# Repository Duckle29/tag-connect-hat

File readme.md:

# Tag connect hat
A hat for a Rasperry Pi, for programming ISP targets with the TC2030-MCP cable

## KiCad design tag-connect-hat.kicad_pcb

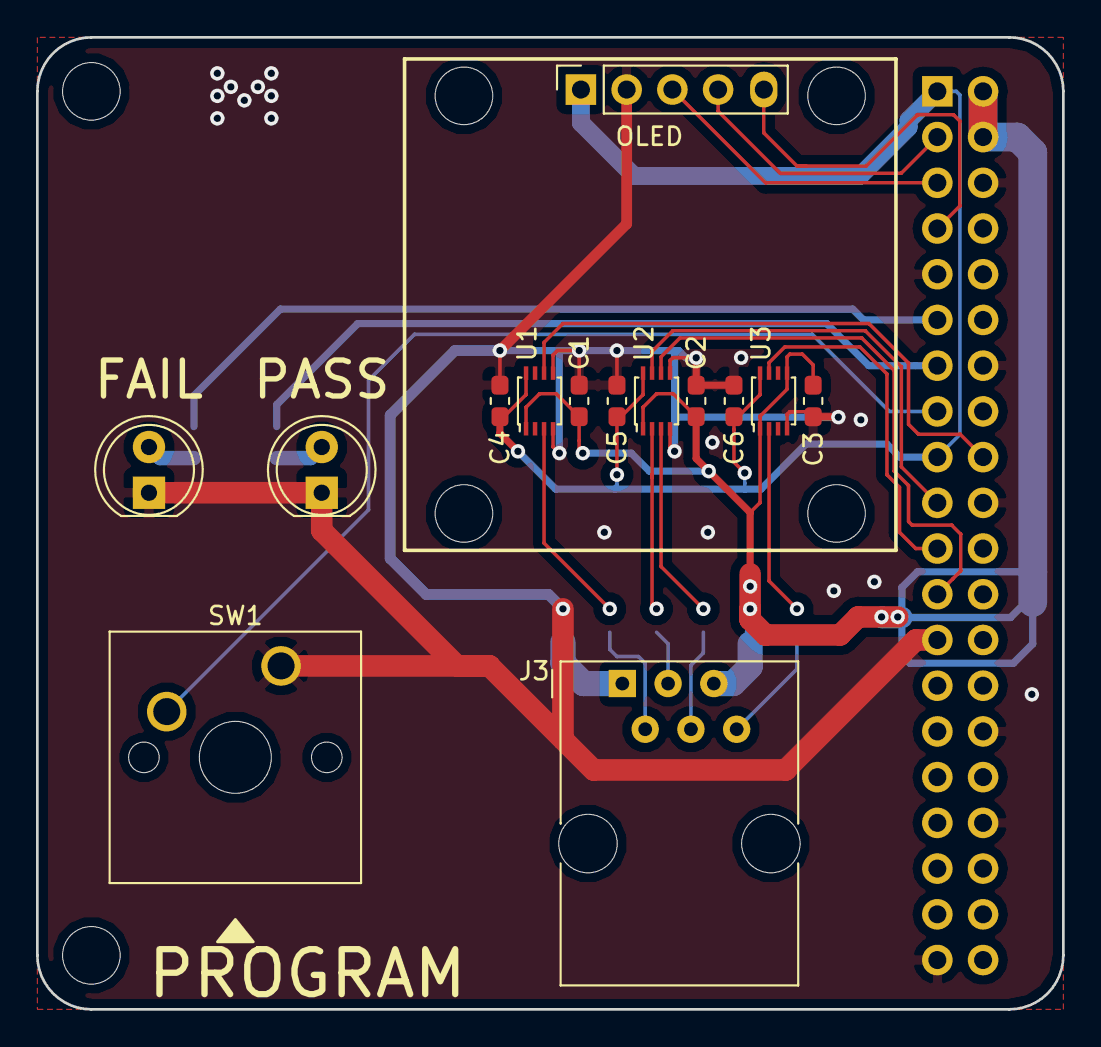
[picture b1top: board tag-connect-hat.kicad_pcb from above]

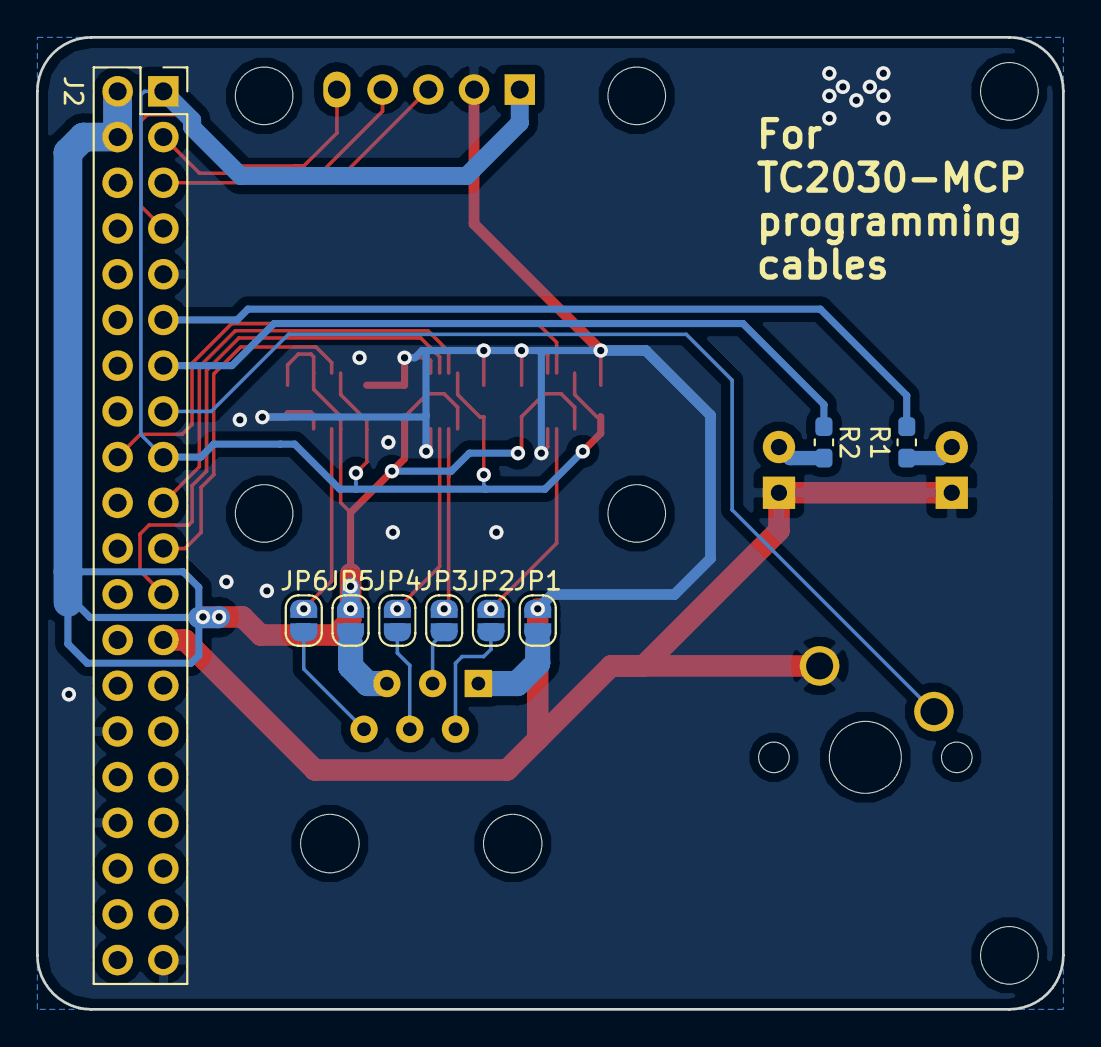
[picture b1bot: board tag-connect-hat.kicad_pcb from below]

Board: 2 copper layers, 57.0 x 54.0 mm, 23 parts (9 on the bottom side), 25 nets.

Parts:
C1, C2, C3, C4, C5, C6: 100nF; C_0603_1608Metric_Pad1.05x0.95mm_HandSolder
D1: Red; LED_D5.0mm_Clear
D2: Green; LED_D5.0mm_Clear
J1: OLED; PinSocket_1x05_P2.54mm_Vertical
J2: Raspberry_Pi_2_3; PinSocket_2x20_P2.54mm_Vertical
J3: RJ12_Shielded; RJ12_Amphenol_54601
JP1, JP2, JP3, JP4, JP5, JP6: Jumper_2_Open; SolderJumper-2_P1.3mm_Open_RoundedPad1.0x1.5mm
R1, R2: 220R; R_0603_1608Metric_Pad1.05x0.95mm_HandSolder
SW1: Button; SW_Cherry_MX1A_1.50u_PCB
U1, U2, U3: 74LVC2T45DC; VSSOP-8_2.4x2.1mm_P0.5mm

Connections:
+3V3: C4.1, C5.1, C6.1, J1.1, J2.1, J2.17, U1.8, U2.8, U3.8
+5V: C1.1, C2.1, C3.1, J2.2, J2.4, JP5.2, U1.1, U2.1, U3.1, U3.5
/Button: J2.15, SW1.2
/I2C_SCL: J1.3, J2.5
/I2C_SDA: J1.4, J2.3
/LED_Bad: J2.11, R1.1
/LED_Good: J2.13, R2.1
/MISO-3v3: J2.21, U3.7
/MISO-5v: JP6.2, U3.2
/MOSI-3v3: J2.19, U2.7
/MOSI-5v: JP3.2, U2.2
/SCLK-3v3: J2.23, U2.6
/SCLK-5v: JP4.2, U2.3
/~OLED_RST: J1.5, J2.7
/~RST-3v3: J2.18, U1.6
/~RST-5v: JP2.2, U1.3
GND: C1.2, C2.2, C3.2, C4.2, C5.2, C6.2, D1.1, D2.1, J1.2, J2.6, J2.9, J2.14, J2.20, J2.25, J2.30, J2.34, J2.39, JP1.2, SW1.1, U1.4, U1.5, U2.4, U2.5, U3.4
unnamed: D1.2, R1.2
unnamed: D2.2, R2.2
unnamed: J3.1, JP1.1
unnamed: J3.2, JP2.1
unnamed: J3.3, JP3.1
unnamed: J3.4, JP4.1
unnamed: J3.5, JP5.1
unnamed: J3.6, JP6.1
